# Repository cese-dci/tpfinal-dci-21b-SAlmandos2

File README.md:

## Trabajo práctico final de la asignatura DCI ##
Este repositorio contiene el trabajo práctico final para la asignatura de Diseño de Circuitos Impresos de la carrera de posgrado de FIUBA.

* Autor: Santiago Nicolas Almandos Marinzulich
* Título corto del trabajo:  Replica Nibble
* Descripción:  Nibble es una consola de videojuegos educacional hecha por vos mismo

## Licencia de este trabajo ##

Este trabajo se encuentra bajo licencia [GNU GPL 3.0](../gpl-3.0.txt)

## Estructura del TP FINAL ##

Se propone y se pide utilizar la siguiente estructura.

* doc: Toda la información sobre el circuito, principalmente de autoría o procesamiento propio. Por ejemplo:
  * Notas de ingeniería propias.
  * Notas de aplicación propias.
  * Estudios previos, estado del arte, resumen de las investigaciones.
  * Notas con cálculos.
  * Dibujos adicionales.
  * Fotos de los prototipos.
  * Presupuestos, cotizaciones.
* info: Toda la iformación recolectada, principalmente de terceros, como por ejemplo:
  * Hojas de datos.
  * Notas de aplicación.
  * Info de productos comerciales.
  * Info en internet.
* pcb: Archivos de diseño esquemático y pcb.

Dependiendo la magnitud del proyecto, tendremos más o menos información en estos directorios. 
Revisar los README.md en cada directorio para conocer las pautas de cada uno para este TP.

NOTA: El alumno puede y debe borrar de este archivo todo lo que considere necesario, por ejemplo las aclaraciones del docente y esta misma nota.

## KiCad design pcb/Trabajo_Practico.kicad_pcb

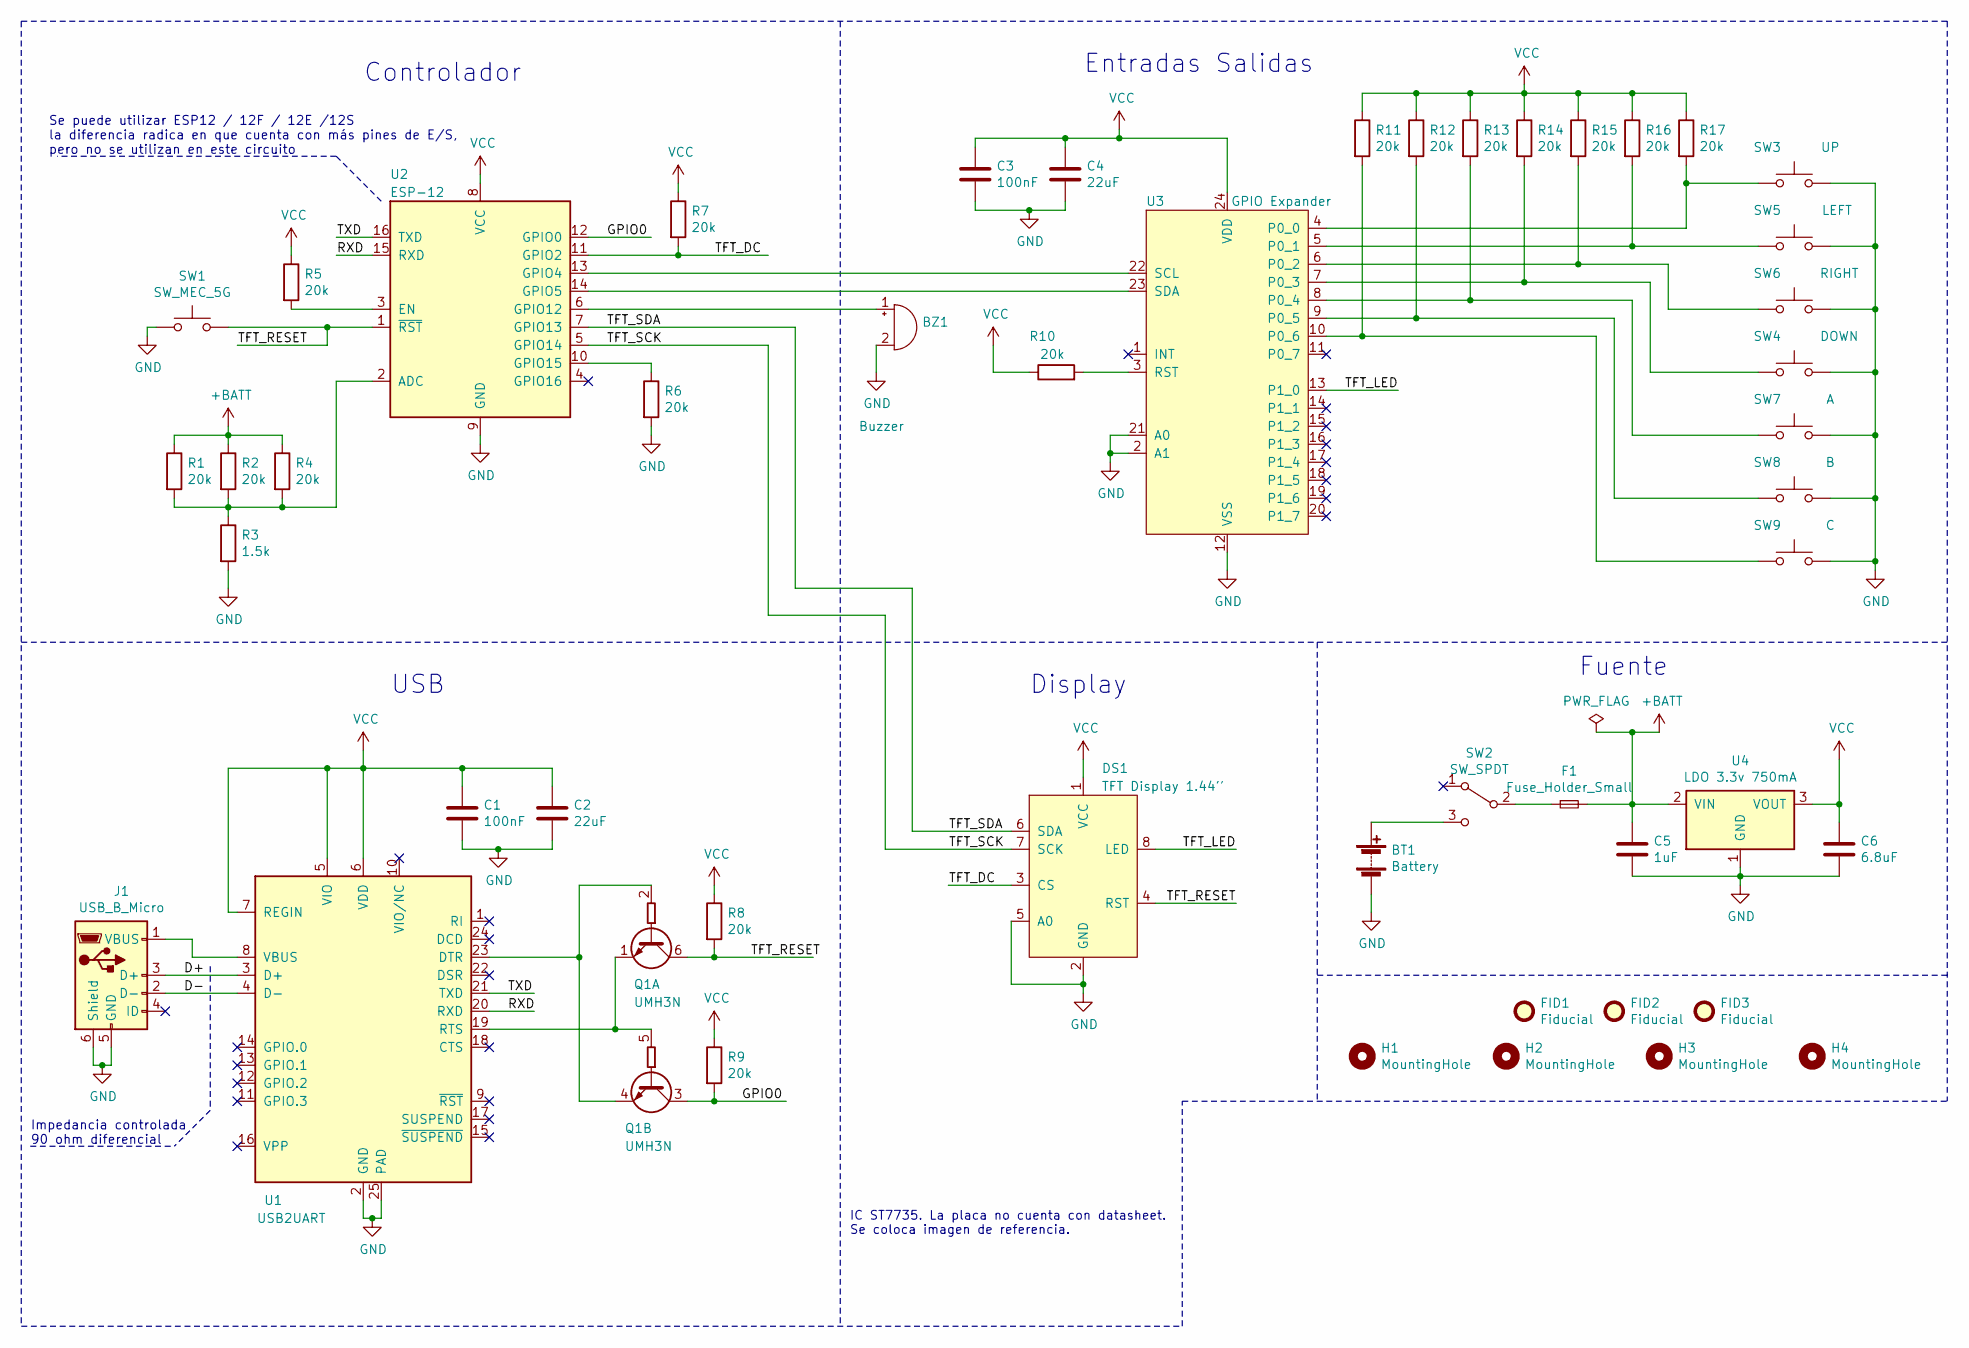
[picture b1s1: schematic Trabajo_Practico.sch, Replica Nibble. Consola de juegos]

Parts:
BT1: Battery; BatteryHolder_Keystone_2479_3xAAA
BZ1: Buzzer; MagneticBuzzer_CUI_CMT-8504-100-SMT; Manuf# CMT-8503-85B-SMT-TR; Mouser 490-CMT-850385BSMTTR
C1, C3: 100nF; C_0805_2012Metric
C2, C4: 22uF; C_0805_2012Metric
C5: 1uF; C_0805_2012Metric
C6: 6.8uF; C_0805_2012Metric
DS1: TFT Display 1.44''; TFT_1.44I_SPI; Manuf# ST7735_1.44_128x128_SPI
F1: Fuse_Holder_Small; Fuse_Holder_Littefuse_Nano; Manuf# 0154001.DRTL
FID1, FID2, FID3: Fiducial; Fiducial_1.5mm_Mask3mm
H1, H2, H3, H4: MountingHole; MountingHole_2.2mm_M2_Pad_Via
J1: USB_B_Micro; USB_Micro-B_Molex_47346-0001; Manuf# 10104110-0001LF; Mouser 649-10104110-0001LF
Q1: UMH3N; SOT-363_SC-70-6; Manuf# UMH3NFHATN; Mouser 755-UMH3NFHATN
R1, R2, R4, R5, R6, R7, R8, R9, R10, R11, R12, R13, R14, R15, R16, R17: 20k; R_0805_2012Metric
R3: 1.5k; R_0805_2012Metric
SW1: SW_MEC_5G; SW_Tactile_SPST_Angled_PTS645Vx31-2LFS
SW2: SW_SPDT; SW_CuK_JS202011AQN_DPDT_Angled
SW3: UP; SW_SPST_PTS645
SW4: DOWN; SW_SPST_PTS645
SW5: LEFT; SW_SPST_PTS645
SW6: RIGHT; SW_SPST_PTS645
SW7: A; SW_SPST_PTS645
SW8: B; SW_SPST_PTS645
SW9: C; SW_SPST_PTS645
U1: USB2UART; QFN-24-1EP_4x4mm_P0.5mm_EP2.6x2.6mm; Manuf# CP2104-F03-GM; Mouser 634-CP2104-F03-GM
U2: ESP-12; ESP-12E
U3: GPIO Expander; TSSOP-24_4.4x7.8mm_P0.65mm; Manuf# PCA9539APW,118; Mouser 771-PCA9539APW,118
U4: LDO 3.3v 750mA; SOT-89-3_Handsoldering; Manuf# H7650-33PR

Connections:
+BATT: C5.1, F1.2, R1.1, R2.1, R4.1, U4.2 (VIN)
/D+: J1.3 (D+), U1.3 (D+)
/D-: J1.2 (D-), U1.4 (D-)
/GPIO0: Q1.3 (C2), R9.2, U2.12 (GPIO0)
/RXD: U1.20 (RXD), U2.15 (RXD)
/TFT_DC: DS1.3 (CS), R7.2, U2.11 (GPIO2)
/TFT_LED: DS1.8 (LED), U3.13 (P1_0)
/TFT_RESET: DS1.4 (RST), Q1.6 (C1), R8.2, SW1.3 (B), SW1.4 (B), U2.1 (~RST)
/TFT_SCK: DS1.7 (SCK), U2.5 (GPIO14)
/TFT_SDA: DS1.6 (SDA), U2.7 (GPIO13)
/TXD: U1.21 (TXD), U2.16 (TXD)
GND: BT1.2 (-), BZ1.2 (+), C1.2, C2.2, C3.2, C4.2, C5.2, C6.2, DS1.2 (GND), DS1.5 (A0), J1.5 (GND), J1.6 (Shield), R3.2, R6.2, SW1.1 (A), SW1.2 (A), SW3.2, SW4.2, SW5.2, SW6.2, SW7.2, SW8.2, SW9.2, U1.2 (GND), U1.25 (PAD), U2.9 (GND), U3.2 (A1), U3.12 (VSS), U3.21 (A0), U4.1 (GND)
unnamed: BT1.1 (+), SW2.3 (C)
unnamed: BZ1.1 (-), U2.6 (GPIO12)
unnamed: F1.1, SW2.2 (B)
unnamed: J1.1 (VBUS), U1.8 (VBUS)
unnamed: Q1.1 (E1), Q1.5 (B2), U1.19 (RTS)
unnamed: Q1.2 (B1), Q1.4 (E2), U1.23 (DTR)
unnamed: R1.2, R2.2, R3.1, R4.2, U2.2 (ADC)
unnamed: R5.2, U2.3 (EN)
unnamed: R6.1, U2.10 (GPIO15)
unnamed: R10.2, U3.3 (RST)
unnamed: R11.2, SW9.1, U3.10 (P0_6)
unnamed: R12.2, SW8.1, U3.9 (P0_5)
unnamed: R13.2, SW7.1, U3.8 (P0_4)
unnamed: R14.2, SW4.1, U3.7 (P0_3)
unnamed: R15.2, SW6.1, U3.6 (P0_2)
unnamed: R16.2, SW5.1, U3.5 (P0_1)
unnamed: R17.2, SW3.1, U3.4 (P0_0)
unnamed: U2.13 (GPIO4), U3.22 (SCL)
unnamed: U2.14 (GPIO5), U3.23 (SDA)
VCC: C1.1, C2.1, C3.1, C4.1, C6.1, DS1.1 (VCC), R5.1, R7.1, R8.1, R9.1, R10.1, R11.1, R12.1, R13.1, R14.1, R15.1, R16.1, R17.1, U1.5 (VIO), U1.6 (VDD), U1.7 (REGIN), U2.8 (VCC), U3.24 (VDD), U4.3 (VOUT)

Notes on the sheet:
Controlador
Entradas Salidas
Display
USB
Fuente
IC ST7735. La placa no cuenta con datasheet. Se coloca imagen de referencia.
Se puede utilizar ESP12 / 12F / 12E /12S la diferencia radica en que cuenta con más pines de E/S, pero no se utilizan en este circuito
Impedancia controlada 90 ohm diferencial

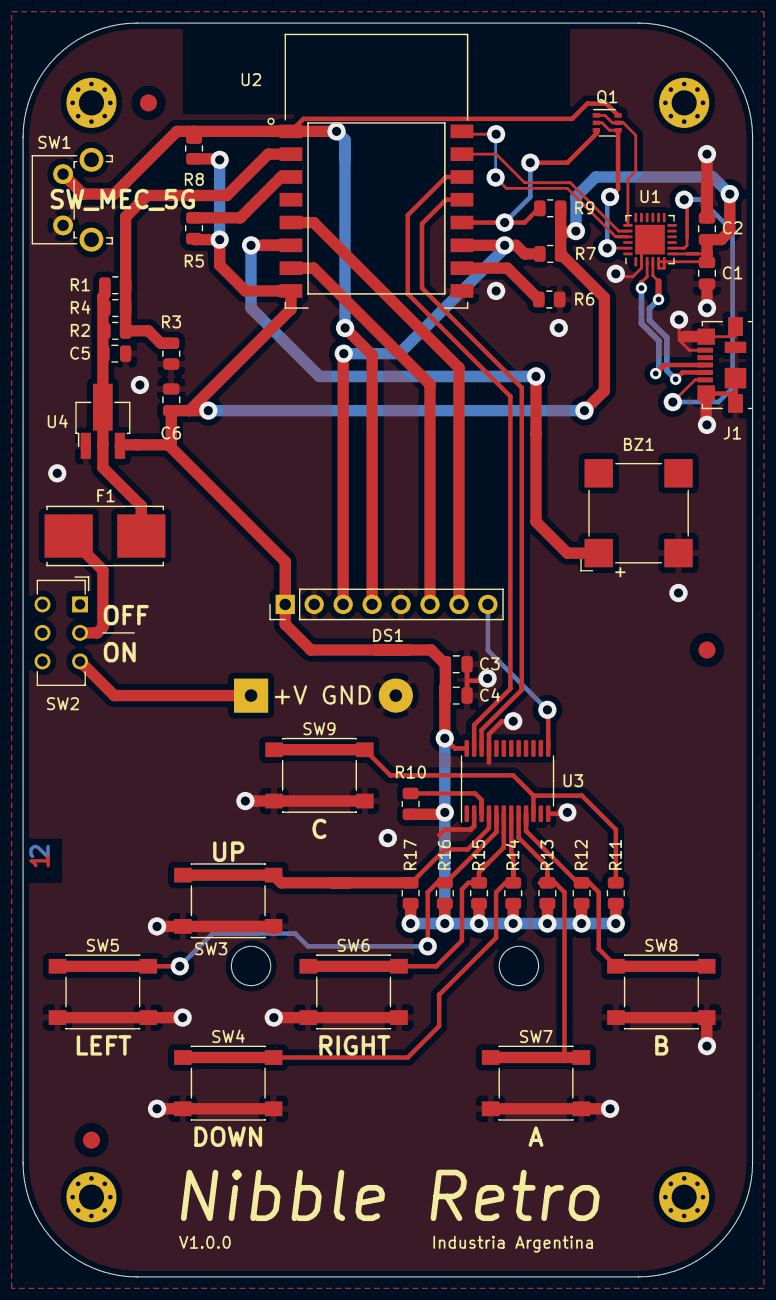
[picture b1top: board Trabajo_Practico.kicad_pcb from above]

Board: 2 copper layers, 64.0 x 110.0 mm, 49 parts (1 on the bottom side), 32 nets.

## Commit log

2021-07-04 Agregado proyecto y esquematicos
2021-08-01 Actualizacion de documentos y esquematico
2021-08-08 Updated PCB component place and board edge
2021-08-08 Removed old Library files
2021-08-11 modified switch to SMD
2021-08-14 Routed and checked
2021-08-17 added all 3d shapes
2021-08-22 Fix: clearance to 0.25 and values in schematic
2021-08-22 Fix: layer num on notes
